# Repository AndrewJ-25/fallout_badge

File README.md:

# Fallout Name Badge

Slack user: Andrew Jia

UHF civilian CW transceiver using ESP32-C3 and radio module. Name tag for the real Andrew, not SanfrAndrew (he's larping)

PCB nametag built for Fallout

## Render

## Schematic

## PCB

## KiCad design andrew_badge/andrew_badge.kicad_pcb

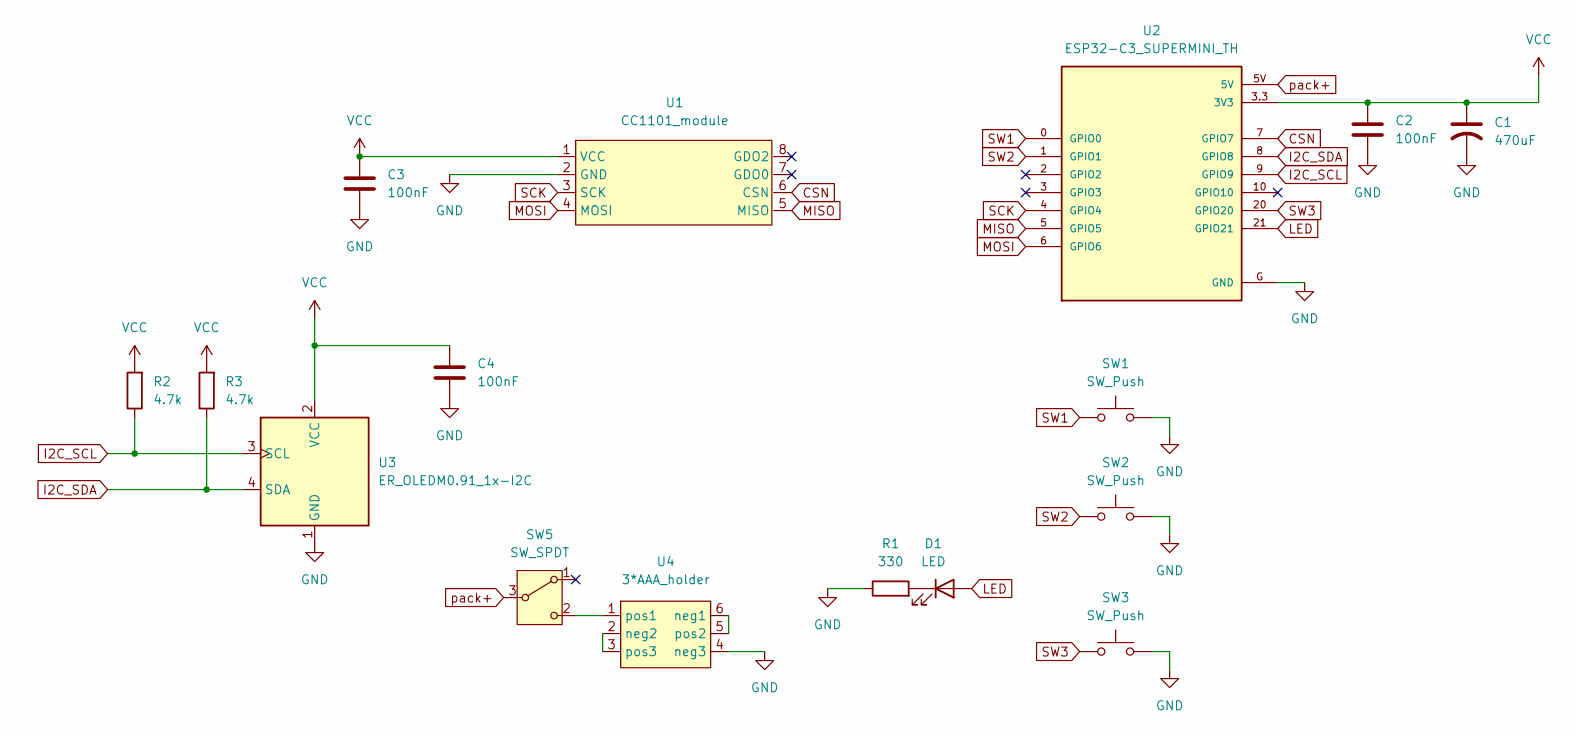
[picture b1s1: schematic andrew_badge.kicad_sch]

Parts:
C1: 470uF; C_Disc_D5.0mm_W2.5mm_P2.50mm
C2: 100nF; CP_Radial_D5.0mm_P2.00mm
C3, C4: 100nF; C_Disc_D5.0mm_W2.5mm_P2.50mm
D1: LED; LED_D3.0mm
R1: 330; R_Axial_DIN0207_L6.3mm_D2.5mm_P7.62mm_Horizontal
R2, R3: 4.7k; R_Axial_DIN0207_L6.3mm_D2.5mm_P7.62mm_Horizontal
SW1, SW2, SW3: SW_Push; SW_PUSH_6mm
SW5: SW_SPDT; SW_Slide_SPDT_Angled_CK_OS102011MA1Q
U1: CC1101_module
U2: ESP32-C3_SUPERMINI_TH; MODULE_ESP32-C3_SUPERMINI_TH
U3: ER_OLEDM0.91_1x-I2C
U4: 3*AAA_holder; 3xAAA_SMD

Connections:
CSN: U1.6 (CSN), U2.7 (GPIO7)
GND: C1.2, C2.2, C3.2, C4.2, R1.1, SW1.2, SW2.2, SW3.2, U1.2 (GND), U2.G (GND), U3.1 (GND), U4.4 (neg3)
I2C_SCL: R2.1, U2.9 (GPIO9), U3.3 (SCL)
I2C_SDA: R3.1, U2.8 (GPIO8), U3.4 (SDA)
LED: D1.2 (A), U2.21 (GPIO21)
MISO: U1.5 (MISO), U2.5 (GPIO5)
MOSI: U1.4 (MOSI), U2.6 (GPIO6)
unnamed: D1.1 (K), R1.2
unnamed: SW5.2 (C), U4.1 (pos1)
unnamed: U4.5 (pos2), U4.6 (neg1)
unnamed: U4.2 (neg2), U4.3 (pos3)
SCK: U1.3 (SCK), U2.4 (GPIO4)
SW1: SW1.1, U2.0 (GPIO0)
SW2: SW2.1, U2.1 (GPIO1)
SW3: SW3.1, U2.20 (GPIO20)
VCC: C1.1, C2.1, C3.1, C4.1, R2.2, R3.2, U1.1 (VCC), U2.3.3 (3V3), U3.2 (VCC)
pack+: SW5.3 (B), U2.5V

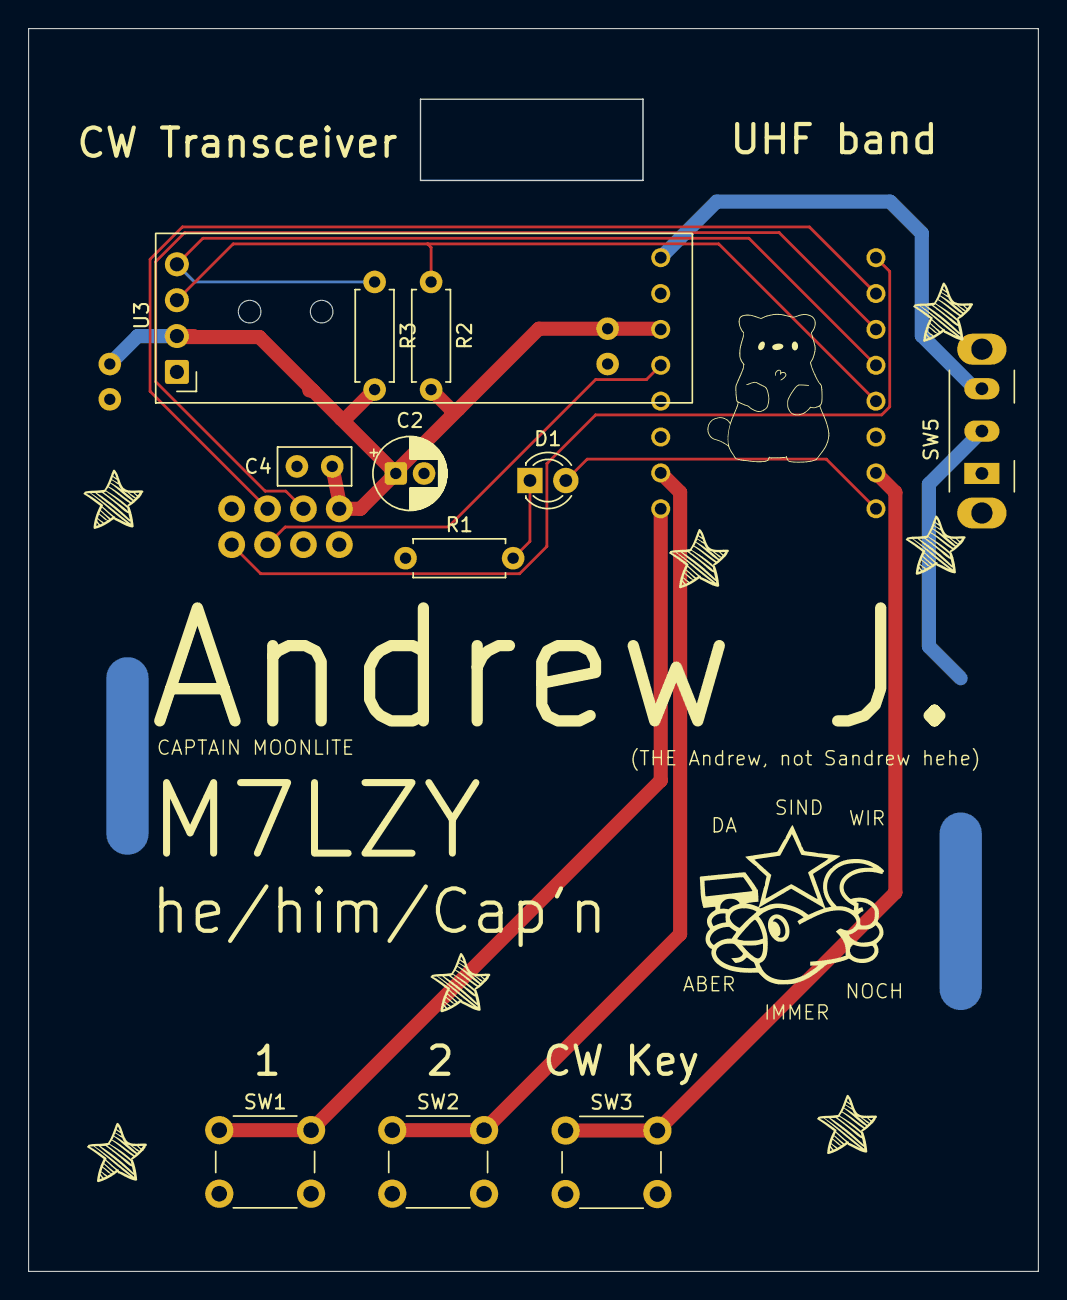
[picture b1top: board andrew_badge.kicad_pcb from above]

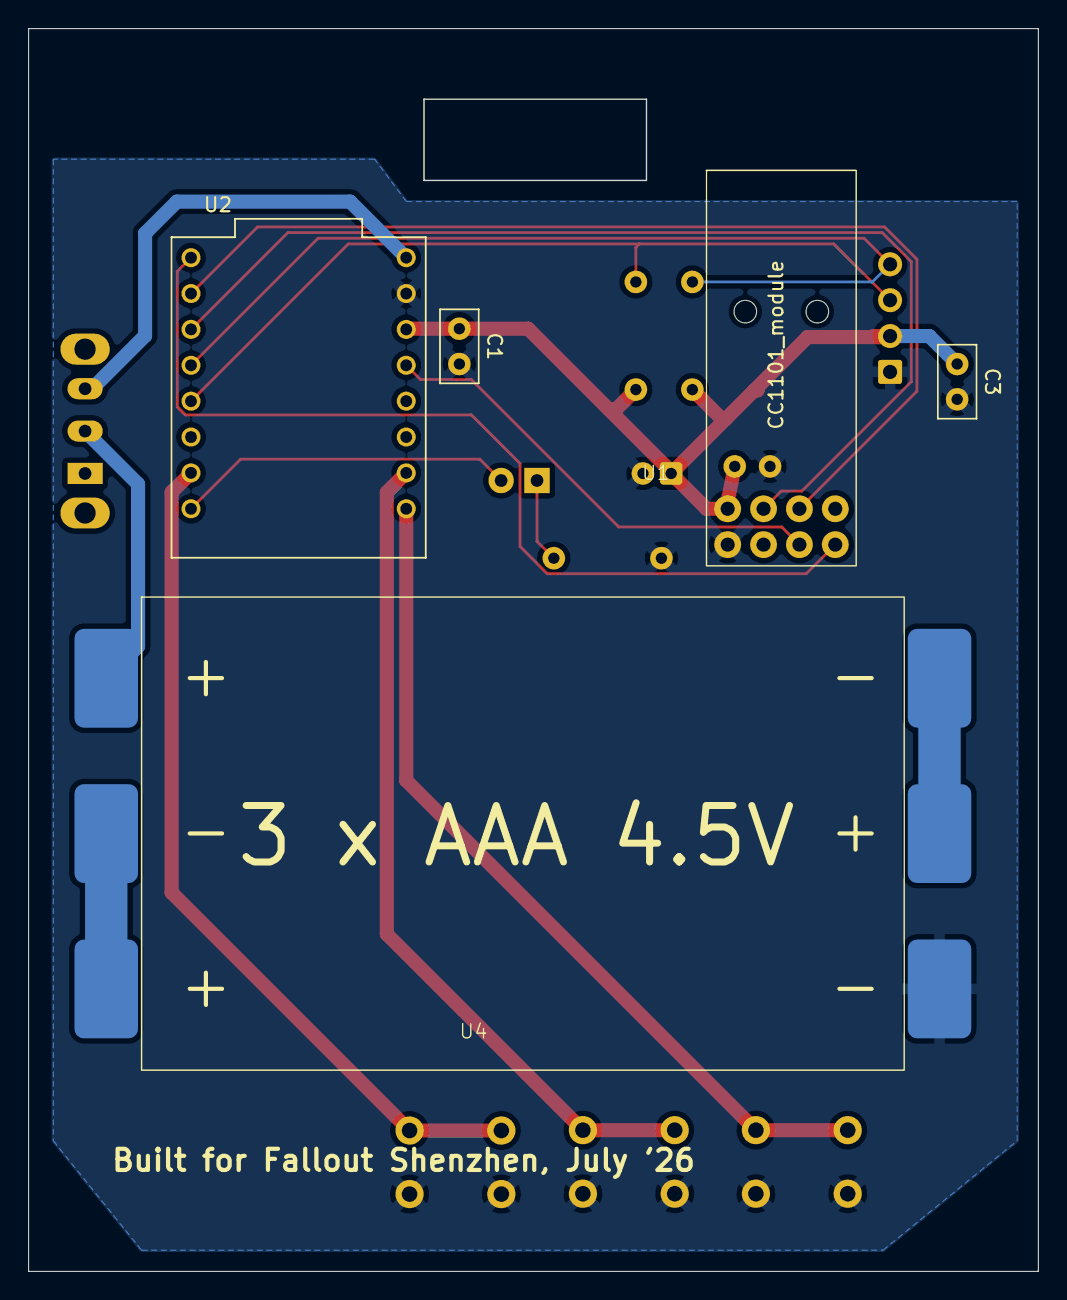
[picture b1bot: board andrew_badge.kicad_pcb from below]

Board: 2 copper layers, 71.5 x 88.0 mm, 16 parts (5 on the bottom side), 17 nets.
